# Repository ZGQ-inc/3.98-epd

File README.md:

# 3.98" BWRY 墨水屏随身伴侣 · Open E-Badge & Ita-Bag

<p align="center">
  <b>无需局域网 Wi-Fi · 手机 Chrome 蓝牙直连 · 100% 离线 PWA · Cloudflare Pages 免费一键托管</b><br>
  专为 3.98 英寸四色电子墨水屏打造的随身工牌、电子名片、兽聚痛卡与智能留言板开源软硬件全栈解决方案。
</p>

<p align="center">

</p>

---

## 🌟 项目亮点 (Highlights)

1. **彻底告别 Wi-Fi 局域网依赖 (Zero Wi-Fi Needed)**:
   - 随身携带在展会、地铁、办公室或户外时，无需路由器局域网。
   - 打开手机或电脑 Chrome / Edge 浏览器访问部署好的 PWA 网页，点击“连接蓝牙”即可通过 Web Bluetooth API 直接与 3.98" 墨水屏握手直推。
2. **免费静态托管于 Cloudflare Pages**:
   - 纯前端无服务器架构（HTML5 + Canvas + Pure JS + Service Worker）。
   - 零成本全球 CDN 极速分发与自动权威 HTTPS（满足 Chromium WebBLE API 强制安全上下文要求）。
3. **100% 离线 PWA 支持 (Offline PWA)**:
   - 首次访问后，Service Worker 会将点阵字库生成器、二维码引擎和 4色微粒抖动算法缓存在本地。
   - 即使断网、飞行模式或深处地下场馆，依然能秒速打开并向墨水屏推送。
4. **四大随身定制工坊 (4 Built-in Studios)**:
   - 📇 **智能工牌 / 电子名片 (Smart E-Badge)**: 极客黑客、商务简约、同人展会等高对比度大字模板，内置零依赖纯离线二维码生成器。
   - 🎒 **兽聚痛卡 / 角色挂件 (Anime Ita-Bag Charm)**: 配合外壳双挂绳孔，相册选图、自由缩放/旋转、4色微粒抖动还原，个性台词题字。
   - 📝 **随身便签 / 留言板 (Memo & Checklist)**: 超大字号待办清单，方框复选框，磁吸/挂绳一目了然。
   - 🎨 **4色像素手绘画板 (BWRY Paint Canvas)**: 黑/白/红/黄 4色调色盘，画笔、矩形、圆形、题字、橡皮与撤销功能。
5. **极客级 3D 打印三明治外壳设计 (Optimized Enclosure)**:
   - **三明治三层坚固架构**: 前盖 + 中框 + 后盖独立分层，8 颗 M2 热熔铜螺母高强度锁合（前盖 4 颗 + 中框 4 颗）。
   - **防脱落滑动按键推钮**: 外露手按长度 1.5mm，加厚 7.0mm，四边 45° 倒角，内部防脱咬合卡块卡死后盖限位槽，杜绝脱落丢失。
   - **双挂绳孔**: 屏幕 FPC 一侧居中打 2 个穿绳孔（孔径 1.5mm，孔距 6mm），并带内部穿绳导引沉槽。
   - **前后双 NFC 贴片槽**: 中框正中心 + 后盖屏幕排线侧半边居中，适配 **NTAG216** (25mm 直径) 888 字节大容量贴片。
   - **4 颗强力吸附磁铁**: 后盖内壁预留 4 个 N52 钕铁硼磁铁沉孔（直径 6.0mm），可直接吸附在金属痛包或冰箱表面。

---

## 🗂️ 规范项目目录结构 (Repository Layout)

```text
.
├── README.md               # 项目主说明文档 (功能概览 / 快速编译与刷机指引)
├── BOM.md                  # 详尽硬件物料选型、采购单价与硬核避坑总结 (单一事实来源)
├── LICENSE                 # MIT 开源授权协议
├── .gitignore              # Git 忽略规则 (过滤 target/、编译缓存及临时文件)
│
├── hardware/               # 硬件与 3D 打印外壳工程
│   ├── README.md           # 3D 打印参数推荐与三明治全套组装指导
│   ├── enclosure_vector_mockup.svg # 外壳 1:1 矢量设计展示图
│   ├── 3d_models/          # 即用型 3D 打印 STL 模型与 OpenSCAD 源码
│   │   ├── case_front.stl  # 前框 (正面 6.9mm 窄边框，M2 铜螺母预埋孔)
│   │   ├── case_middle.stl # 中框 (双挂绳孔 1.5mm，正面 25mm NFC 槽，双 Type-C，'O'/`|` 开关标识)
│   │   ├── case_back.stl   # 标准后盖 (FPC 侧居中 25mm NFC 槽，4 个磁铁沉孔，电池防挤压圆角)
│   │   ├── case_back_logo.stl # 定制后盖 (带 "Made by ZGQ Inc." 凹刻文字)
│   │   ├── switch_cap.stl  # 防脱滑动推钮 (外露 1.5mm，卡紧后盖限位槽，4 道防滑齿)
│   │   ├── acrylic_template.stl # 91.0×64.0×1.5mm 亚克力视窗 1:1 划线切割模板
│   │   └── epd_case.scad   # 完整的 OpenSCAD 参数化建模源码
│   ├── scripts/
│   │   └── build_epd_case.py # Python 3D 网格生成脚本 (纯数学算法 + Delaunay 三角剖分)
│   └── fpc_adapter/        # 24-Pin 0.8mm 转 0.5mm 45° 转接板历史归档工程
│
├── cf_pages/               # 部署至 Cloudflare Pages 的 100% 离线独立 PWA 控制端
│   ├── README.md           # Cloudflare Pages 部署说明
│   ├── index.html          # 单页应用 (包含工牌、痛卡、便签、手绘 4 大工坊与 WebBLE 驱动)
│   ├── manifest.json       # PWA 应用配置清单
│   ├── sw.js               # Service Worker 离线缓存引擎 (v2.9)
│   ├── icon-192.svg        # 192x192 矢量图标
│   └── icon-512.svg        # 512x512 高清矢量图标
│
├── tools/                  # 开放式 HTTP 2bpp 推送工具箱与 Python 示例
│   ├── README.md           # 详细 REST API 接口规范与第三方生态接入指引
│   └── epd_push.py         # 任意图片转 2bpp / 自动立绘旋转 / HTTP 推送 CLI & SDK
│
├── firmware/               # 预编译纯净固件与刷机指南
│   ├── README.md           # 详细环境配置与烧录步骤
│   └── epd-firmware.bin    # 预编译好的 1.76MB 裸机启动镜像 (即刷即用)
│
├── src/                    # Rust ESP-IDF 嵌入式主固件源码
│   ├── main.rs             # 系统启动入口、低功耗管理、任务并发调度
│   ├── ble/                # BLE 5.0 GATT 服务定义、流式点阵直推与无刷新预设协议
│   ├── display/            # 2bpp 硬件显存、无闪烁局刷与汉字字库渲染引擎
│   ├── storage/            # 1.5MB SPIFFS 效果库存储管理与物理配额统计
│   ├── modes/              # 工牌、痛卡、时钟、天气与便签模式逻辑
│   ├── power/              # 电源管理、电池电压 ADC 采样与休眠控制
│   ├── web/                # 内嵌轻量级 HTTP Web 服务器与 REST API
│   └── wifi/               # Wi-Fi 局域网通信与 AP 自动配网
│
├── web_assets/             # 编译期内嵌至固件的本地 Web 控制台静态资源
│   ├── index.html          # 局域网控制台 (已支持一键自定义配置您的专属 PWA 网址)
│   ├── index.html.gz       # 极速传输的 Gzip 压缩包
│   └── pwa.html            # 设备内置备用 PWA 页面
│
├── Cargo.toml              # Rust 项目依赖声明 (已配置 strip 自动剥离符号)
├── partitions.csv          # ESP32-C3 4MB Flash 分区表 (2MB App + 1.5MB SPIFFS 效果库)
└── sdkconfig.defaults      # ESP-IDF 系统底层配置 (启用蓝牙射频共存与蓝牙 5.0)
```

---

## 📋 硬件物料清单 (BOM)

关于器件的具体选型背景（**20~25 元华为生态四色墨水屏手机壳尾货捡漏实录**、高压驱动电压避坑、**663032 750mAh 锂电池**选型、**三明治 8 颗 M2 铜螺母锁固**及 NTAG216 智能名片细节），请直接参阅独立的硬件物料清单文档：

👉 **[硬件物料选型与采购清单 (BOM.md)](hardware/BOM.md)**

---

## 💻 固件编译与刷机指引 (Compilation & Flashing)

本项目主固件基于 **Rust ESP-IDF** 体系打造，针对 **ESP32-C3 (RISC-V 32位架构)** 进行了极致汇编与内存优化。

### 1. 为什么未剥离的 ELF 文件会有 20MB+？
在 `target/.../release/` 下生成的 `epd-firmware` 文件是标准的 RISC-V ELF 格式，包含了大量的 **DWARF 调试符号表**（`.debug_info`、`.debug_line`、函数符号与源码行号映射等，用于 GDB/LLDB 断点调试）。  
我们已在 `Cargo.toml` 中配置了 `debug = 0` 与 `strip = true`：
```toml
[profile.release]
opt-level = "z"
lto = "fat"
panic = "abort"
debug = 0
strip = true
```
真正烧录进单片机 Flash 的纯二进制镜像（.bin 文件）仅为 **1,764,592 字节（约 1.68 MB）**，完全适配 ESP32-C3 4MB Flash 的 **2MB 固件分区**（占用率 84.14%）。

---

### 2. 编译环境准备 (Prerequisites)

1. **安装 Rust 工具链**:
   ```bash
   curl --proto '=https' --tlsv1.2 -sSf https://sh.rustup.rs | sh
   ```
2. **安装 ESP32-C3 RISC-V 交叉编译器与烧录工具**:
   ```bash
   cargo install espup
   espup install
   cargo install espflash
   ```
3. **加载 ESP 编译环境变量**:
   - **Windows PowerShell**:
     ```powershell
     . $HOME/export-esp.ps1
     ```
   - **Linux / macOS**:
     ```bash
     source ~/export-esp.sh
     ```

---

### 3. 一键编译与固件导出

在项目根目录下执行：
```bash
# 1. 编译 release 生产模式固件
cargo +esp build --release

# 2. 将 ELF 可执行文件剥离并保存为单片机纯二进制镜像 (.bin)
espflash save-image --chip esp32c3 target/riscv32imc-esp-espidf/release/epd-firmware firmware/epd-firmware.bin
```

---

### 4. 烧录到设备 (Flash to ESP32-C3)

将 ESP32-C3 SuperMini 通过 Type-C 数据线连接至电脑：

#### 方式一：使用 `espflash` 自动烧录（最推荐）
```bash
# 自动探测串口并烧录
espflash flash --release

# 或指定具体串口号（例如 Windows 上的 COM17，Linux 上的 /dev/ttyUSB0）
espflash flash --port COM17 --release
```

#### 方式二：免编译直接烧录预编译镜像 (.bin)
仓库已在 `firmware/epd-firmware.bin` 预先提供了最新编译好的裸机固件。您可以使用 Python 的 `esptool.py` 直接刷入：
```bash
esptool.py --chip esp32c3 -p <PORT> -b 460800 write_flash 0x20000 firmware/epd-firmware.bin
```

---

### 5. Flash 分区表规划 (Partitions Layout)

4MB Flash 布局严格按照 `partitions.csv` 划分：

| 分区名 | 类型 | 子类型 | 偏移地址 | 大小 | 作用说明 |
| :--- | :--- | :--- | :--- | :--- | :--- |
| `nvs` | data | nvs | `0x9000` | 24 KB | 存储 Wi-Fi 凭据、蓝牙名称与模式持久配置 |
| `phy_init` | data | phy | `0x11000` | 4 KB | 射频初始化与天线校准数据 |
| `factory` | app | factory | `0x20000` | 2048 KB (2.0 MB) | Rust ESP-IDF 主固件代码段 (当前占用约 84%) |
| `font` | data | 0x01 | `0x220000` | 288 KB | Flash MMU 零内存占用标准点阵中文字库 |
| `storage` | data | spiffs | `0x268000` | 1632 KB (~1.6 MB) | 单片机内置 SPIFFS 效果库 (真实物理存储) |

---

### 6. 连电脑用命令恢复出厂设置与防死锁救砖 (Factory Reset & Unbricking)

系统在 PWA / 本地 Web 控制台 / 蓝牙 BLE 发起「恢复出厂设置」时，**会同时彻底清空 NVS 参数配置分区与 Storage 效果库预设分区**（恢复至裸机出厂态，并重启进入 AP 配网热点与 BLE 广播）。

若在操作射频模式时不慎将 Wi-Fi 与蓝牙设置为死锁/失联状态，可通过 Type-C 数据线将 ESP32-C3 连接至电脑，使用以下命令免拆机 1 秒恢复出厂设置：

#### 方案一：彻底恢复出厂设置（同时擦除 NVS 参数配置与 Storage 效果库）
```bash
# 擦除 0x9000 (NVS 24KB) 与 0x268000 (Storage 1632KB)
python -m esptool --chip esp32c3 -p <PORT> erase_region 0x9000 0x6000
python -m esptool --chip esp32c3 -p <PORT> erase_region 0x268000 0x198000
```

#### 方案二：仅清除配置参数（保留已保存的效果库预设文件）
只需擦除 `0x9000` 处的 NVS 分区（大小 24 KB），设备即可在**不损坏主固件、字库与已保存预设**的前提下重置 Wi-Fi/模式参数：
```bash
# 推荐方式 A：使用本工程内置的 espflash 工具：
espflash erase-parts --port COM17 --partition-table partitions.csv nvs

# 方式 B：使用 Python esptool 工具：
python -m esptool --chip esp32c3 -p COM17 erase_region 0x9000 0x6000
```
执行完毕后，重新插拔 USB 或按一下板载 Reset 键，设备即以出厂默认状态启动。

#### 方案三：全片擦除并重新刷机（终极救砖）
```bash
# 1. 彻底擦除 4MB Flash
python -m esptool --chip esp32c3 -p <PORT> erase_flash

# 2. 重新刷入最新编译的二进制固件
python -m esptool --chip esp32c3 -p <PORT> write_flash 0x20000 firmware/epd-firmware.bin
```

---

### 7. 屏幕硬件规格版本切换 (A0 / A1 扫描走线)

华为手机保护壳拆机的 3.98 英寸 BWRY 四色电子墨水屏通常存在两款不同的物理硬件批次：`SE0398NZ07-FNG-A0` 与 `A1`。
两者的差异在于内部 Gate 扫描引脚在玻璃基板上的交错走线映射方式不同。如果驱动版本选错，屏幕画面会出现**隔行交错条纹、半屏错位或上下撕裂**。

本项目已实现 **NVS 动态配置与免编译一键切换**：

1. **PWA 随身工坊（支持蓝牙 BLE 直连 / 局域网 Wi-Fi）**：
   - 打开 PWA 页面，进入 **「⚙️ 硬件诊断」** 选项卡；
   - 顶部提供 **「🖥️ 墨水屏硬件规格版本 (A0 / A1 扫描走线)」** 开关卡片；
   - 点击 **`A0 走线 (默认)`** 或 **`A1 走线`**，配置将即时写入单片机 NVS，并自动触发墨水屏物理重绘全刷。
2. **设备内置 Web 控制台**：
   - 浏览器直接访问设备 IP（如 `http://192.168.4.1` 或局域网分配 IP）；
   - 在控制台系统诊断区域直接点击 **A0 / A1** 单选按钮即可立即生效。
3. **固件默认值修改（可选编译配置）**：
   - 固件源码中默认采用 `A0` 规格；若希望编译一份开机即默认以 `A1` 运行的固件，可直接修改 `src/config/mod.rs` 中的 `default_panel_version()` 返回值为 `"A1"`。

---

## 🌐 开放式 HTTP 2bpp 点阵推送 API (Open REST API)

为方便任意外部系统（**Home Assistant 智能家居、Android Automate/Tasker、Python 脚本、树莓派、我的台式机、我的 GPD 掌机、cURL、服务器监控**）向工牌推送显示内容，固件原生提供免绑定的 **RESTful HTTP 原始位图裸推接口**：

* **API 端点**: `POST http://<设备IP或域名>/api/push/raw` *(支持 mDNS: `http://epd-display.local/api/push/raw`)*
* **请求头**: `Content-Type: application/octet-stream`
* **数据规格**: 严格 **105,984 字节** 的 2bpp 二进制流（768×552 BWRY 4色点阵，每字节打包 4 像素）
* **参数选项**: `?refresh=false` 或 `X-Refresh: false`（仅写入显存，暂不触发 16 秒硬件波形刷新）

### ⚡ 3 种极简调用示例

#### 1. cURL 单行命令直接推送现有点阵文件
```bash
curl -X POST --data-binary @image.2bpp http://epd-display.local/api/push/raw
```

#### 2. Python 转换任意图片并推送 (推荐使用内置工具)
本项目在 `tools/` 目录提供了全功能的图片转 2bpp 及网络推送工具：
```bash
# 安装依赖
pip install pillow requests

# 一键推送任意图片至工牌
python tools/epd_push.py photo.png --host epd-display.local

# 兽聚痛卡 / 二次元竖屏立绘自适应旋转模式 (-p)
python tools/epd_push.py character.png -p --host epd-display.local

# 仅导出 .2bpp 二进制文件与四色预览图 (不发送请求)
python tools/epd_push.py input.jpg -o output.2bpp --preview preview.png --dry-run
```

#### 3. Python SDK 代码集成
```python
from tools.epd_push import image_to_2bpp, push_to_epd

# 转换图片为 105KB 2bpp 点阵
raw_bytes = image_to_2bpp("avatar.png", portrait=True, dither="floyd")

# 推送至局域网工牌
res = push_to_epd(raw_bytes, host="epd-display.local")
print(res)  # {'success': True, 'status': 'ok', 'message': '...'}
```

👉 **更详细的接口规范、2bpp 像素位编码格式与 Home Assistant 自动化配置，请参阅：[开放式 HTTP 推送 API 与工具箱文档 (tools/README.md)](tools/README.md)**

---

## 🛡️ 蓝牙双向设备管理、动态 PIN 码配对与 NFC 碰一碰秒绑 (Two-Way Device Management & Security)

为了让墨水屏能够安全、可靠地佩戴于漫展、聚会与公共场合，固件与前端 PWA 提供了完整的**双向设备管理与硬件级防骚扰安全认证体系**：

### 1. 为什么必须具备硬件级会话认证与防骚扰？
- **保护双稳态屏幕寿命与电量**：四色电子墨水屏物理刷新一次需 16 秒并消耗毫安级电量。若蓝牙广播处于完全开放裸奔状态，任何经过的陌生人均可在手机浏览器通过 WebBLE 下发指令频繁刷屏骚扰或篡改显示画面。
- **连接不扰动原则**：蓝牙物理连接建立时，**墨水屏物理屏幕绝不意外闪烁或刷新**！屏幕保持原展示画面不变。

### 2. 双向设备管理架构 (Two-Way Architecture)
- **控制端 (浏览器 / PWA 侧)**：
  - 用户可在「我的墨水屏徽章库」中同时管理与记忆多台墨水屏（如：`3.98吋工牌-兽聚痛卡挂件`、`我的桌面副屏时钟`、`冰箱贴留言板`）；
  - 支持分别设置自定义徽章别名，点击即可一键秒速重连。
- **墨水屏硬件端 (ESP32 NVS 永久白名单)**：
  - 硬件 NVS 独立维护 `trusted_devices` 控制端白名单列表（如：`主力机三星 Fold7`、`我的台式机`、`备用机红米`、`我的 GPD 掌机`、`朋友的手机`）；
  - 只有处于白名单中且持有随机分配 `token` 的控制端才能向墨水屏下发推送点阵、切换模式或刷新指令；
  - 主人可在 PWA 控制台中对白名单中的控制端进行**重命名**或**解除授权/删除**；一旦从白名单中删除，该设备即刻失去控制权。

### 3. 开箱首次配对与动态 PIN 码流程 (OOB PIN Pairing)
1. **未配对接入确认**：全新浏览器连接时，PWA 会弹出确认弹窗。若用户选择「取消断开」，蓝牙立即断开且墨水屏**不刷新**；
2. **6 位动态 PIN 码卡片**：用户点击「开始 PIN 配对」后，墨水屏屏幕刷新显示大字版 6 位动态 PIN 码（120 秒防暴力破解倒计时）；
3. **安全注册写入 NVS**：用户在 PWA 弹窗中输入屏幕上的 6 位 PIN 码并为控制端命名（支持智能预填：如检测到 Android 手机自动预填 `主力机三星 Fold7` 或 `备用机红米`，检测到 Windows PC 自动预填 `我的台式机` 或 `我的 GPD 掌机`），验证通过后在硬件 NVS 写入唯一设备 ID 与令牌，墨水屏自动切至【配对成功与 NFC 钥匙指引】界面。

### 4. NFC 物理电子钥匙一碰秒绑 (Zero-PIN NFC Claim)
- **硬件随机主密钥**：单片机在每次开机时若检测到未生成过密钥，将调用 ESP32 硬件真随机数发生器 (`esp_random()`) 自动生成唯一 16 字节 Master Key 永久存入 NVS（出厂恢复或老固件 OTA 均能自愈）；
- **写入贴纸标签**：在 PWA 设备管理中点击「碰一碰将钥匙写入 NFC 标签」，通过 Web NFC（或复制链接用 NFC Tools）将 `https://398epd.zgqinc.gq/#key=<32位密钥>` 写入贴在墨水屏背面或挂绳上的 NTAG 标签；
- **新设备一碰秒绑**：外出时新设备（或朋友手机）只需碰一下墨水屏背面的 NFC 标签，浏览器打开 PWA 后通过 URL Hash（仅保存在浏览器客户端，零网络泄露）自动读取钥匙并一键秒速完成白名单绑定，完全免去开机看屏输 PIN 码！

### 5. 漫展防骚扰开关 (Anti-DoS PIN Disable)
- 主人完成设备初次配对后，可在 PWA 设备管理中一键关闭「屏幕 PIN 码配对」；
- 关闭后，陌生人在公共场合无法触发屏幕 PIN 码配对，彻底杜绝恶意蹭连与耗电刷屏骚扰；只有碰一碰物理 NFC 钥匙或已有白名单设备方可操控。

---

## 🚀 1 分钟一键部署至 Cloudflare Pages

1. Fork 本仓库到你自己的 GitHub 账号；
2. 登录 [Cloudflare Dashboard](https://dash.cloudflare.com/)，点击 **Workers & Pages** -> **Create application** -> **Pages** -> **Connect to Git**；
3. 选择该仓库，配置构建参数：
   - **Framework preset**: `None`
   - **Build command**: *(留空)*
   - **Build output directory**: `cf_pages`
4. 点击 **Save and Deploy**，30 秒后即可获得免费的全球 CDN HTTPS 域名（例如: `https://my-epd-badge.pages.dev`）！
5. 在手机或电脑 Chrome / Edge 浏览器打开该网址，点击“连接蓝牙”即可开箱即用。

---

## 📄 开源许可证 (License)

本项目采用 [MIT 许可证](LICENSE) 开源，欢迎自由构建、修改、二次开发与商业/非商业分享！

> 💡 **关于版权与署名说明**：  
> 版权声明中的 `ZGQ Inc.` 仅为作者个人昵称（Author Handle）。本项目全栈源代码、固件、前端 PWA 及相关硬件工程文件均遵循宽松的 **MIT 许可证** 开放授权，任何人均可在遵守并保留 MIT 许可证声明的前提下自由使用、修改与衍生开发。

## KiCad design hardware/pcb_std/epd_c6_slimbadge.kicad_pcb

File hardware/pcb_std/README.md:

# SlimBadge-C6 Standard 标准版 (全功能平衡)

## 1. 版本定位与成本
- **定位**：全功能平衡版，支持 NFC 交互、RTC 极低功耗待机、IMU 计步/姿态唤醒、MicroSD/TF 卡扩展与电量精确监控。
- **BOM 器件数**：40 项 (主板) + 1 项 (FPC NFC 天线)。
- **单套预估成本**：约 ¥84.19。

## 2. 关键硬件变更说明
1. **移除 CH224K PD 诱骗芯片**：
   - 采用标准 5.1k CC 下拉，直接从 USB Type-C 端口安全取电 5V，彻底消除 9V 降压带来的发热与电容耐压隐患。
2. **新增侧按微动轻触按键 (SW2)**：
   - 采用标准超薄侧按轻触开关 `SW_SPST_B3U-3000P`（LCSC: C135850），放置于板边顶部 ($X=13.5, Y=1.7$)。
   - 按键轴心沿 PCB 水平外沿突出 0.25mm，适配外壳侧壁开孔，实现真正的**侧边按压（侧按）**。
   - 信号直连 `GPIO9`，支持一键刷机下载与用户自定义功能（切页/休眠/背光）。
3. **新增 6 位镀金调试测试焊盘矩阵 (TP1 ~ TP6)**：
   - 利用原 CH224K 区域布局 6 个 1.2mm 镀金测试点：`VBUS`、`3V3`、`BAT`、`BOOT` 及双 `GND`，外围标注清晰丝印，便于出厂测试与探针测试。
4. **板载 SPI Flash (U12) 3D 模型修复**：
   - 绑定物理 SOIC-8 3D 模型，3D 视图与渲染图均完整呈现元器件实体。

## 3. 生产文件
- PCB: `epd_c6_slimbadge.kicad_pcb`
- SCH: `epd_c6_slimbadge.kicad_sch`
- SMT BOM: `BOM_JLCSMT_SlimBadge_C6.csv`
- CPL: `CPL_JLCSMT_SlimBadge_C6.csv`

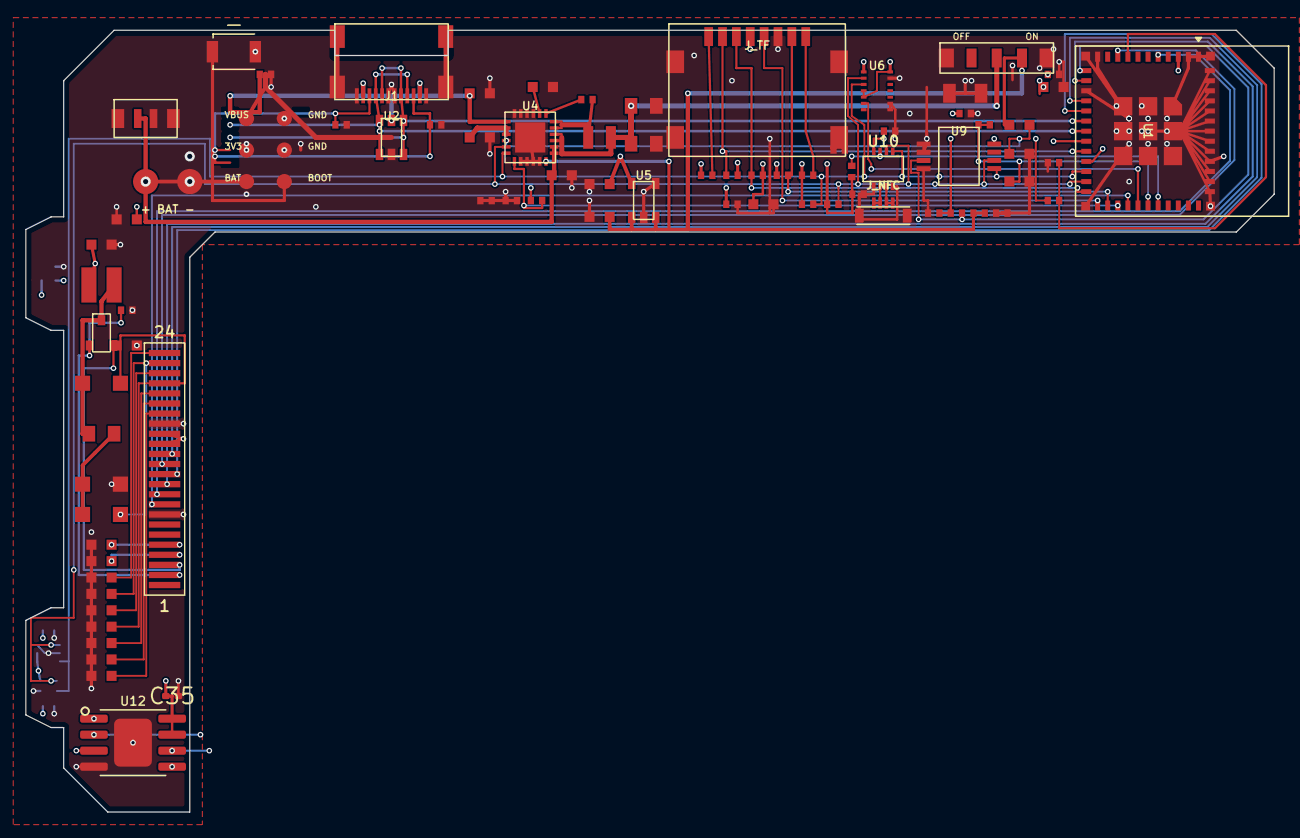
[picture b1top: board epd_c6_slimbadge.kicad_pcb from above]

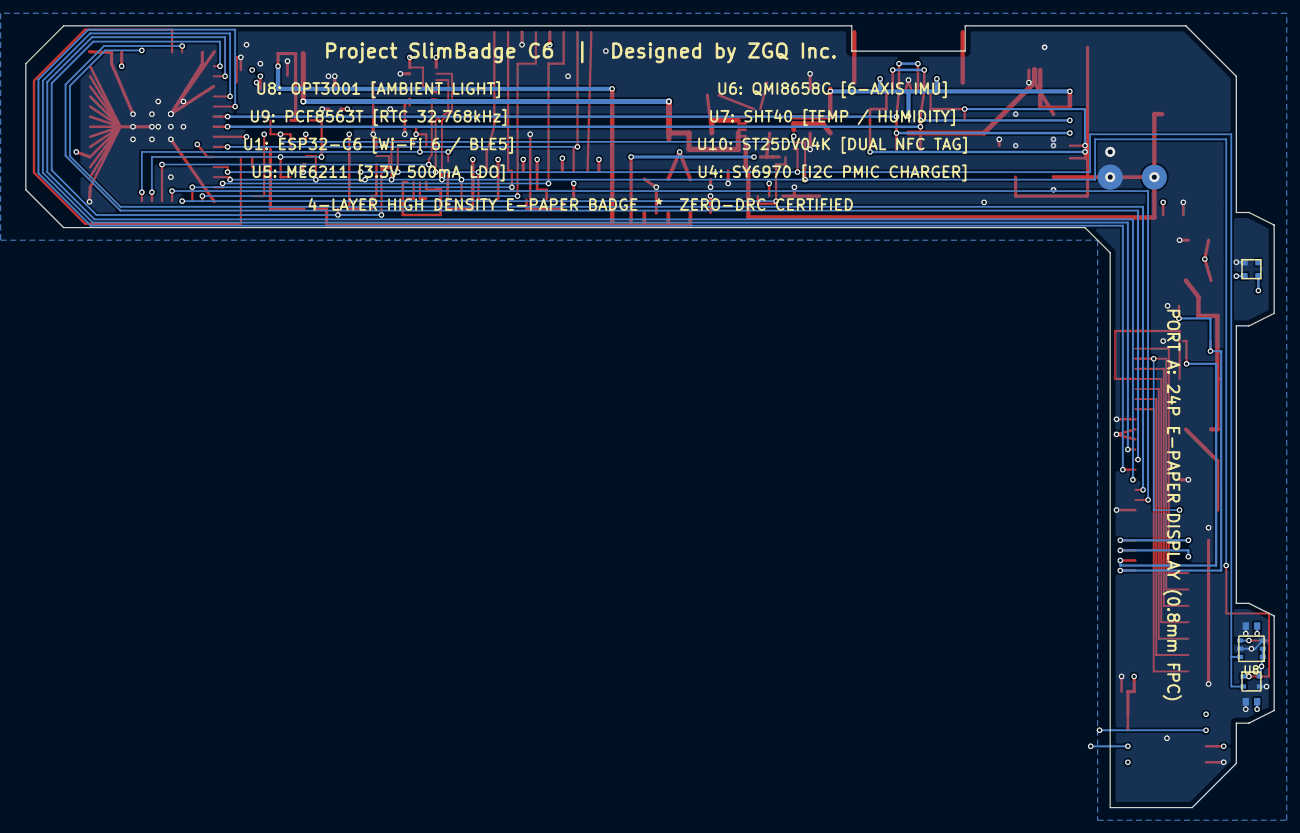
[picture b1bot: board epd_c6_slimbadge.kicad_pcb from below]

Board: 4 copper layers, 99.0 x 62.0 mm, 93 parts (7 on the bottom side), 53 nets.

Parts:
C1, C23: 4.7uF; C_0603_1608Metric
C2: 4.7uF_50V; C_0805_2012Metric
C3: 1uF; C_0402_1005Metric
C4, C19, C24, C25, C27: 10uF; C_0603_1608Metric
C5, C6, C7, C8, C9, C10, C11, C12, C13, C14: 1uF_50V; C_0603_1608Metric
C15, C16, C22, C26, C28, C29, C30, C31, C32, C33, C34: 0.1uF; C_0402_1005Metric
C17: 1uF_25V; C_0603_1608Metric
C18: 10uF_25V; C_0603_1608Metric
C20, C21: 22uF; C_0805_2012Metric
C35: 0.1uF
D1, D3, D4: MBR0540; D_SOD-123
J1: Type-C_16P; USB_C_Receptacle_MidMount
J2: JST_1.25mm_2P; JST_GH_SM02B-GHS-TB_1x02-1MP_P1.25mm_Horizontal
J_EPD_A: EPD_PortA_0.8mm; 0.8mm_24P
J_NFC: FPC_0.5mm_4P
J_TF: MicroSD_MidMount; microSD_HC_Hirose_DM3D-SF
L1: 68uH; L_1210_3225Metric
L2: 1.0uH; L_1210_3225Metric
LED1: SK6805-EC15; LED_SK6805_1515
LED2: CHG_Red; LED_0603_1608Metric
LED3: DONE_Green; LED_0603_1608Metric
LED4: ACT_White; LED_0603_1608Metric
PAD_BAT_N: BAT-; TestPoint_Pad_D2.0mm
PAD_BAT_N_B: BAT-_B; TestPoint_Pad_D2.0mm
PAD_BAT_P: BAT+; TestPoint_Pad_D2.0mm
PAD_BAT_P_B: BAT+_B; TestPoint_Pad_D2.0mm
Q1: AO3400A; SOT-23
R1, R9, R11, R14, R16, R17, R18, R19, R20, R21, R23: 10k; R_0402_1005Metric
R2, R3: 4.7k; R_0402_1005Metric
R5, R22, R24: 1k; R_0402_1005Metric
R7, R8: 5.1k; R_0402_1005Metric
R12: 2.2R; R_0603_1608Metric
R13: 120R; R_0402_1005Metric
SW1: SK12D07; SW_SPDT_PCM12
SW2: B3U-3000P; SW_SPST_B3U-3000P
TP1: VBUS; TestPoint_Pad_D1.2mm
TP2, TP4: GND; TestPoint_Pad_D1.2mm
TP3: 3V3; TestPoint_Pad_D1.2mm
TP5: BAT; TestPoint_Pad_D1.2mm
TP6: BOOT; TestPoint_Pad_D1.2mm
U1: ESP32-C6-MINI-1
U2: USBLC6-2SC6; SOT-23-6
U4: SY6970; QFN-24-1EP_4x4mm_P0.5mm_EP2.6x2.6mm
U5: ME6211C33M5G; SOT-23-5
U6: QMI8658C; LGA-14_2.5x3mm_P0.5mm
U7: SHT40; Sensirion_DFN-4-1EP_1.5x1.5mm_P0.8mm_EP0.6x0.9mm
U8: OPT3001; Texas_S-PDSO-N6
U9: PCF8563T; TSSOP-8_4.4x3mm_P0.65mm
U10: ST25DV04K; UFDFPN-8_2x3mm_P0.5mm
U12: FLASH_4-128MB
Y1: 32.768kHz; Crystal_SMD_3215-2Pin_3.2x1.5mm

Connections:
ACT_LED: LED4.1, R5.1, R5.2, U1.30
BAT_RAW: C19.1, J2.1, PAD_BAT_P.1, PAD_BAT_P_B.1, TP5.1, U4.13, U4.14
BTST_CHG: C22.1, U4.19
CC1: J1.A5, R7.1
CC2: J1.B5, R8.1
CHG_INT: R11.2, U1.27, U4.7
CHG_STAT: LED2.2, LED3.1, U4.4
CHIP_EN: C3.1, R1.2, U1.8
EPD_BUSY: J_EPD_A.9, U1.28
EPD_CP: C2.2, D3.1, D4.1
EPD_CS: J_EPD_A.12, U1.16
EPD_DC: J_EPD_A.11, U1.13
EPD_DIN: J_EPD_A.14, U1.15
EPD_GDR: J_EPD_A.2, Q1.1, R9.1
EPD_RESE: J_EPD_A.3, Q1.2, R12.1
EPD_RST: J_EPD_A.10, U1.5
EPD_SCK: J_EPD_A.13, U1.9
EPD_SW: C2.1, D1.1, L1.2, Q1.3
EPD_VCOM: C14.2, J_EPD_A.24
EPD_VDD: C8.2, J_EPD_A.18
EPD_VGH: C6.2, J_EPD_A.5
EPD_VGL: C5.2, J_EPD_A.4
EPD_VPP: C9.2, J_EPD_A.19
EPD_VSH1: C10.2, J_EPD_A.20
EPD_VSL: C12.2, J_EPD_A.22
FLASH_CS: U1.21, U12.1
GND: C1.2, C3.2, C4.2, C5.1, C6.1, C7.1, C8.1, C9.1, C10.1, C11.1, C12.1, C13.1, C14.1, C15.2, C16.2, C17.2, C18.2, C19.2, C20.2, C21.2, C23.2, C24.1, C25.1, C26.2, C27.2, C28.2, C29.2, C30.2, C31.2, C32.1, C32.2, C33.2, C34.2, C35.2, D4.2, J1.A1, J1.A8, J1.B1, J1.B8, J1.SH1, J1.SH2, J1.SH3, J1.SH4, J2.2, J2.MP1, J2.MP2, J_EPD_A.8, J_EPD_A.17, J_NFC.MP1, J_NFC.MP2, J_TF.6, J_TF.SH1, J_TF.SH2, J_TF.SH3, J_TF.SH4, LED1.4, LED3.2, LED4.2, PAD_BAT_N.1, PAD_BAT_N_B.1, R7.2, R8.2, R9.2, R12.2, R13.1, R13.2, R14.1, R14.2, R24.1, R24.2, SW1.SH1, SW1.SH2, SW2.2, TP2.1, TP4.1, U1.1, U1.2, U1.11, U1.14, U1.36, U1.37, U1.38, U1.39, U1.40, U1.41, U1.42, U1.43, U1.44, U1.45, U1.46, U1.47, U1.48, U1.49, U1.50, U1.51, U1.52, U1.53, U2.2, U4.8, U4.9, U4.10, U4.11, U4.21, U4.22, U4.23, U4.24, U4.25, U5.2, U5.4, U6.8, U6.9, U6.13, U7.4, U8.3, U8.5, U9.1, U9.2, U9.4, U10.1, U10.4, U12.4, U12.9, Y1.1, Y1.2
GPIO9: SW2.1, TP6.1
I2C_SCL: R3.2, U1.23, U4.5, U6.2, U7.2, U8.4, U9.6, U10.6
I2C_SDA: R2.2, U1.22, U4.6, U6.3, U7.1, U8.6, U9.5, U10.5
IMU_INT: U1.29, U6.6
NFC_AC0: J_NFC.1, J_NFC.2, U10.2
NFC_AC1: J_NFC.3, J_NFC.4, U10.3
NFC_GPO: R23.2, U1.31, U10.7
PMID: C18.1, U4.2, U4.3
PREVGH: C11.2, D1.2, J_EPD_A.21
PREVGL: C13.2, D3.2, J_EPD_A.23
REGN_CHG: C23.1, U4.20
RGB_DIN: LED1.1, U1.19
RTC_INT: R21.2, U1.12, U9.3
SD_CS: J_TF.2, R17.2, U1.20
SD_DAT1: J_TF.8, R20.2
SD_DAT2: J_TF.1, R16.2
SD_MISO: J_TF.7, R19.2, U1.26, U12.2
SD_MOSI: J_TF.3, R18.2, U1.24, U12.5
SD_SCK: J_TF.5, U1.25, U12.6
SW_CHG: C22.2, L2.1, U4.17, U4.18
USB_D+: J1.A6, J1.B6, U1.18, U2.1, U2.6
USB_D-: J1.A7, J1.B7, U1.17, U2.3, U2.4
VBUS: C16.1, C17.1, J1.A4, J1.B4, TP1.1, U2.5, U4.1
VCC_3V3: C1.1, C4.1, C7.2, C15.1, C25.2, C26.1, C27.1, C28.1, C29.1, C30.1, C31.1, C33.1, C34.1, C35.1, J_EPD_A.15, J_EPD_A.16, J_TF.4, L1.1, LED1.2, R1.1, R2.1, R3.1, R11.1, R16.1, R17.1, R18.1, R19.1, R20.1, R21.1, R23.1, TP3.1, U1.3, U5.5, U6.1, U6.4, U6.5, U6.14, U7.3, U8.1, U8.2, U9.8, U10.8, U12.3, U12.7, U12.8
VCC_SYS: C24.2, LED2.1, R22.1, R22.2, SW1.3, U4.12, U5.1, U5.3
VCC_SYS_IN: C20.1, C21.1, L2.2, SW1.2, U4.15, U4.16

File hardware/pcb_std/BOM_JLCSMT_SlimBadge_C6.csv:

Comment,Designator,Footprint,LCSC Part #
4.7uF_50V,C2,Capacitor_SMD:C_0805_2012Metric,C98192
1uF,C3,Capacitor_SMD:C_0402_1005Metric,C5137499
10uF,"C4,C19,C24,C25,C27",Capacitor_SMD:C_0603_1608Metric,C19702
1uF_50V,"C5,C6,C7,C8,C9,C10,C11,C12,C13,C14",Capacitor_SMD:C_0603_1608Metric,C15849
0.1uF,"C15,C16,C22,C26,C28,C29,C30,C31,C32,C33,C34,C35",Capacitor_SMD:C_0402_1005Metric,C1525
1uF_25V,C17,Capacitor_SMD:C_0603_1608Metric,C15849
10uF_25V,C18,Capacitor_SMD:C_0603_1608Metric,C96446
22uF,"C20,C21",Capacitor_SMD:C_0805_2012Metric,C45783
4.7uF,"C1,C23",Capacitor_SMD:C_0603_1608Metric,C19666
MBR0540,"D1,D3,D4",Diode_SMD:D_SOD-123F,C77337
Type-C_16P_MidMount,J1,Connector_USB:USB_C_Receptacle_Palconn_UTC16-G,C2765186
SH1.0mm_2P_Battery,J2,Connector_JST:JST_SH_SM02B-SRSS-TB_1x02-1MP_P1.00mm_Horizontal,C41431902
FPC_0.5mm_4P,J_NFC,Connector_FFC-FPC:FPC_0.5mm_4P_Horizontal,C510961
SIM-004X,J_TF,Connector_Card:microSD_HC_Hirose_DM3D-SF,C183629
68uH,L1,Inductor_SMD:L_3012_3x3mm,C497561
1.0uH,L2,Inductor_SMD:L_2520_2.5x2mm,C98348
SK6805-EC15,LED1,LED_SMD:LED_SK6805_1515,C2890035
CHG_Red,LED2,LED_SMD:LED_0603_1608Metric,C51933292
DONE_Green,LED3,LED_SMD:LED_0603_1608Metric,C84267
ACT_White,LED4,LED_SMD:LED_0603_1608Metric,C84265
AO3400A,Q1,Package_TO_SOT_SMD:SOT-23,C20917
10k,"R1,R9,R11,R14,R16,R17,R18,R19,R20,R21,R23",Resistor_SMD:R_0402_1005Metric,C25744
4.7k,"R2,R3",Resistor_SMD:R_0402_1005Metric,C25900
5.1k,"R7,R8",Resistor_SMD:R_0402_1005Metric,C25905
2.2R,R12,Resistor_SMD:R_0603_1608Metric,C23345
120R,R13,Resistor_SMD:R_0402_1005Metric,C2909315
1k,"R5,R22,R24",Resistor_SMD:R_0402_1005Metric,C2906864
MSK12C02,SW1,Button_Switch_SMD:SW_SPDT_PCM12,C431540
ESP32-C6-MINI-1-N4,U1,RF_Module:ESP32-C6-MINI-1,C5736265
USBLC6-2SC6,U2,Package_TO_SOT_SMD:SOT-23-6,C7519
SY6970,U4,Package_DFN_QFN:QFN-24-1EP_4x4mm_P0.5mm_EP2.6x2.6mm,C5357542
ME6211C33M5G,U5,Package_TO_SOT_SMD:SOT-23-5,C15651
QMI8658C,U6,Package_LGA:LGA-14_2.5x3mm_P0.5mm,C3021082
AHT20,U7,Package_DFN_QFN:Sensirion_DFN-4-1EP_1.5x1.5mm_P0.8mm_EP0.6x0.9mm,C2757850
OPT3001,U8,Package_SON:Texas_S-PDSO-N6,C90462
PCF8563DTR,U9,Package_SO:TSSOP-8_4.4x3mm_P0.65mm,C18723596
ST25DV04K,U10,Package_SO:UFDFPN-8_2x3mm_P0.5mm,C2908287
XT25F128FWOIGT,U12,Package_SO:SOIC-8_208mil_WSON-8_8x6mm_DualCombo,C42162960
32.768kHz,Y1,Crystal:Crystal_SMD_3215-2Pin_3.2x1.5mm,C32346
B3U-3000P,SW2,Button_Switch_SMD:SW_SPST_B3U-3000P,C135850

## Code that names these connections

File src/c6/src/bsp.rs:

// src/bsp.rs — Project SlimBadge C6 Board Support Package (BSP)
// Target MCU: ESP32-C6 (ESP32-C6-MINI-1-N4)
// Standardized hardware definitions, I2C bus management, and GPIO control.

use esp_idf_hal::gpio::{Input, Output, PinDriver, Pull};
use esp_idf_hal::i2c::{I2cConfig, I2cDriver};
use esp_idf_hal::peripherals::Peripherals;
use esp_idf_hal::units::Hertz;
use log::info;

pub use crate::pins;

/// Status report of discovered I2C devices on the shared bus
#[derive(Debug, Clone, Default)]
pub struct I2cScanReport {
    pub sy6970_found: bool,
    pub qmi8658_found: bool,
    pub sht40_found: bool,
    pub opt3001_found: bool,
    pub pcf8563_found: bool,
    pub st25dv_found: bool,
    pub total_devices_found: usize,
}

/// Hardware interrupt line states
#[derive(Debug, Clone, Copy, PartialEq, Eq)]
pub struct InterruptStatus {
    pub rtc_alarm: bool,
    pub imu_motion: bool,
    pub nfc_field: bool,
    pub charger_event: bool,
}

/// Board Support Package for SlimBadge C6
pub struct Bsp<'d> {
    pub i2c: I2cDriver<'d>,
    pub act_led: PinDriver<'d, Output>,
    pub epd_cs: PinDriver<'d, Output>,
    pub epd_dc: PinDriver<'d, Output>,
    pub epd_rst: PinDriver<'d, Output>,
    pub epd_busy: PinDriver<'d, Input>,
    pub sd_cs: PinDriver<'d, Output>,
    pub touch_0: PinDriver<'d, Input>,
    pub touch_1: PinDriver<'d, Input>,
    pub rtc_int: PinDriver<'d, Input>,
    pub imu_int: PinDriver<'d, Input>,
    pub nfc_gpo: PinDriver<'d, Input>,
    pub chg_int: PinDriver<'d, Input>,
}

impl<'d> Bsp<'d> {
    /// Initialize all hardware peripherals, GPIOs, and the shared I2C bus.
    pub fn init(peripherals: Peripherals) -> anyhow::Result<Self> {
        info!("[BSP] Initializing Project SlimBadge C6 Board Support Package...");

        // 1. Initialize Shared Fast I2C Bus (SDA: GPIO 8, SCL: GPIO 9 @ 400kHz)
        let i2c_config = I2cConfig::new().baudrate(Hertz(400_000)).scl_enable_pullup(true).sda_enable_pullup(true);
        let i2c = I2cDriver::new(
            peripherals.i2c0,
            peripherals.pins.gpio8,
            peripherals.pins.gpio9,
            &i2c_config,
        )?;
        info!("[BSP] I2C0 Bus online (SDA=IO8, SCL=IO9, 400kHz Fast-mode).");

        // 2. Initialize Activity LED (GPIO 16)
        let mut act_led = PinDriver::output(peripherals.pins.gpio16)?;
        act_led.set_low()?;

        // 3. Initialize E-Paper Display Control GPIOs
        let mut epd_cs = PinDriver::output(peripherals.pins.gpio7)?;
        epd_cs.set_high()?; // Deselected

        let mut epd_dc = PinDriver::output(peripherals.pins.gpio1)?;
        epd_dc.set_low()?;

        let mut epd_rst = PinDriver::output(peripherals.pins.gpio2)?;
        epd_rst.set_high()?; // Not in reset

        let epd_busy = PinDriver::input(peripherals.pins.gpio22, Pull::Up)?;

        // 4. Initialize MicroSD SPI Chip Select (GPIO 15)
        let mut sd_cs = PinDriver::output(peripherals.pins.gpio15)?;
        sd_cs.set_high()?; // Deselected

        // 5. Initialize Capacitive Touch Inputs (GPIO 3, GPIO 5)
        let touch_0 = PinDriver::input(peripherals.pins.gpio3, Pull::Down)?;
        let touch_1 = PinDriver::input(peripherals.pins.gpio5, Pull::Down)?;

        // 6. Initialize Hardware Interrupt Lines
        let rtc_int = PinDriver::input(peripherals.pins.gpio0, Pull::Up)?;
        let imu_int = PinDriver::input(peripherals.pins.gpio23, Pull::Down)?;
        let nfc_gpo = PinDriver::input(peripherals.pins.gpio17, Pull::Down)?;
        let chg_int = PinDriver::input(peripherals.pins.gpio21, Pull::Up)?;

        info!("[BSP] All GPIO pin directions and pull-ups configured successfully.");

        Ok(Self {
            i2c,
            act_led,
            epd_cs,
            epd_dc,
            epd_rst,
            epd_busy,
            sd_cs,
            touch_0,
            touch_1,
            rtc_int,
            imu_int,
            nfc_gpo,
            chg_int,
        })
    }

    /// Turn the activity LED on or off
    pub fn set_act_led(&mut self, state: bool) -> anyhow::Result<()> {
        if state {
            self.act_led.set_high()?;
        } else {
            self.act_led.set_low()?;
        }
        Ok(())
    }

    /// Check if the E-Paper Display is currently busy refreshing
    /// In SSD1680 / UC8179 panels, BUSY is Active Low (0=Busy, 1=Idle)
    pub fn is_epd_busy(&self) -> bool {
        self.epd_busy.is_low()
    }

    /// Read touch button inputs: (TOUCH_0 / Left, TOUCH_1 / Right)
    pub fn read_touch_keys(&self) -> (bool, bool) {
        (self.touch_0.is_high(), self.touch_1.is_high())
    }

    /// Read status of all external interrupt lines
    pub fn read_interrupts(&self) -> InterruptStatus {
        InterruptStatus {
            rtc_alarm: self.rtc_int.is_low(),     // Active Low open-drain
            imu_motion: self.imu_int.is_high(),   // Active High push-pull
            nfc_field: self.nfc_gpo.is_high(),    // Active High RF detected
            charger_event: self.chg_int.is_low(), // Active Low open-drain
        }
    }

    /// Scans the I2C bus for all known sensors and peripheral ICs, printing a diagnostic table.
    pub fn scan_and_report_i2c(&mut self) -> I2cScanReport {
        println!("\n+-------------------------------------------------------------+");
        println!("|       SlimBadge C6 - Hardware I2C Device Probe Diagnostic  |");
        println!("+-------------------------------------------------------------+");
        println!("| Address | Device Identity                | Status           |");
        println!("+---------+--------------------------------+------------------+");

        let mut report = I2cScanReport::default();
        let timeout = 100; // 100 ticks

        // Check SY6970
        let res_sy = self.i2c.write(pins::i2c_bus::ADDR_SY6970, &[], timeout).is_ok();
        report.sy6970_found = res_sy;
        if res_sy { report.total_devices_found += 1; }
        println!(
            "|  0x{:02X}   | SY6970 15W Fast Charger / ADC  | {} |",
            pins::i2c_bus::ADDR_SY6970,
            if res_sy { "  DETECTED [✓]   " } else { "  NOT DETECTED   " }
        );

        // Check QMI8658
        let res_imu = self.i2c.write(pins::i2c_bus::ADDR_QMI8658, &[], timeout).is_ok();
        report.qmi8658_found = res_imu;
        if res_imu { report.total_devices_found += 1; }
        println!(
            "|  0x{:02X}   | QMI8658C 6-Axis Motion IMU     | {} |",
            pins::i2c_bus::ADDR_QMI8658,
            if res_imu { "  DETECTED [✓]   " } else { "  NOT DETECTED   " }
        );

        // Check SHT40
        let res_sht = self.i2c.write(pins::i2c_bus::ADDR_SHT40, &[], timeout).is_ok();
        report.sht40_found = res_sht;
        if res_sht { report.total_devices_found += 1; }
        println!(
            "|  0x{:02X}   | SHT40 Temp & Humidity Sensor   | {} |",
            pins::i2c_bus::ADDR_SHT40,
            if res_sht { "  DETECTED [✓]   " } else { "  NOT DETECTED   " }
        );

        // Check OPT3001
        let res_opt = self.i2c.write(pins::i2c_bus::ADDR_OPT3001, &[], timeout).is_ok();
        report.opt3001_found = res_opt;
        if res_opt { report.total_devices_found += 1; }
        println!(
            "|  0x{:02X}   | OPT3001 Ambient Light Sensor   | {} |",
            pins::i2c_bus::ADDR_OPT3001,
            if res_opt { "  DETECTED [✓]   " } else { "  NOT DETECTED   " }
        );

        // Check PCF8563
        let res_rtc = self.i2c.write(pins::i2c_bus::ADDR_PCF8563, &[], timeout).is_ok();
        report.pcf8563_found = res_rtc;
        if res_rtc { report.total_devices_found += 1; }
        println!(
            "|  0x{:02X}   | PCF8563 Ultra-Low Power RTC    | {} |",
            pins::i2c_bus::ADDR_PCF8563,
            if res_rtc { "  DETECTED [✓]   " } else { "  NOT DETECTED   " }
        );

        // Check ST25DV
        let res_nfc = self.i2c.write(pins::i2c_bus::ADDR_ST25DV, &[], timeout).is_ok();
        report.st25dv_found = res_nfc;
        if res_nfc { report.total_devices_found += 1; }
        println!(
            "|  0x{:02X}   | ST25DV04K Dynamic NFC Tag      | {} |",
            pins::i2c_bus::ADDR_ST25DV,
            if res_nfc { "  DETECTED [✓]   " } else { "  NOT DETECTED   " }
        );

        println!("+---------+--------------------------------+------------------+");
        println!("| Probed {} / 6 expected on-board I2C peripherals.            |\n", report.total_devices_found);

        report
    }
}

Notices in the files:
README.md:
MIT License
